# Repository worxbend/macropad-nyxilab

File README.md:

<div align="center">

# 🌙 nyxilab macropad

**12 keys. 2 screens. 16 LEDs. 1 stick *or* 1 knob. 0 glue.**
<br>it's giving main character desk energy 💅

**[✨ product page](https://worxbend.github.io/macropad-nyxilab/) · [📖 docs](https://worxbend.github.io/macropad-nyxilab/guide/) · [🧊 3D viewer](https://worxbend.github.io/macropad-nyxilab/guide/viewer.html) · [⬇️ downloads](https://worxbend.github.io/macropad-nyxilab/guide/downloads.html)**

</div>

## tl;dr 🫠

a hand-wired, 3D-printed macropad built around a **Raspberry Pi Pico 2**, with two color
displays, 16 RGB LEDs, and your pick of an analog thumbstick or a clicky rotary knob. this
monorepo has literally everything: the parametric case, print-ready files, blueprints,
a soldering guide with wiring maps, and the firmware. clone it, print it, solder it, flex it.
no custom PCB, no extra USB socket, no cap.

## choose your fighter 🎮

same case, same keys, same screens, same LEDs. only the thing in the middle changes,
and each edition is its own pair of projects.

| 🕹️ **joystick edition** | 🎛️ **rotary edition** |
|---|---|
|  |  |
| KY-023 thumbstick: mouse, scroll or arrow keys, per layer | KY-040 encoder + a chunky printed Ø48 knob: volume, undo/redo, scroll, zoom… |
| [`joystick/cad`](joystick/cad) · [`joystick/firmware`](joystick/firmware) | [`rotary/cad`](rotary/cad) · [`rotary/firmware`](rotary/firmware) |
| `nyxilab-macropad-joystick-pico2.uf2` | `nyxilab-macropad-rotary-pico2.uf2` |
| [read more →](joystick/README.md) | [read more →](rotary/README.md) |

the frame and the bar-display spine are literally the same parts in both, so switching
teams later means reprinting the top plate and the base. that's it.

## the specs (no cap) 📋

| | |
|---|---|
| ⌨️ **inputs** | 12 × MX switches (hand-wired matrix + diodes) and a KY-023 thumbstick that clicks **or** a KY-040 knob that clicks |
| 📺 **screens** | 1.9" 170×320 ST7789 IPS (main character) + 2.25" 76×284 ST7789P3 bar (the sidekick) |
| 💡 **lights** | 2 × 8 WS2812B LED sticks on the base, either side of the Pico: layer color, breathing or rainbow |
| 🧠 **brain** | Pico 2 (RP2350) USB-C clone, or the OG Pico (RP2040) if that's what you've got |
| 📐 **case** | 3-layer wedge: top plate, contrasting centre frame, base · 10° tilt · 159 × 98 mm · 18 → 35 mm tall |
| 🔩 **held together by** | 8 × M3×8 countersunk screws into heat-set inserts. zero glue, fully serviceable |
| ⚡ **firmware** | USB keyboard + media + mouse, layers, tap-hold, macros, joystick modes or per-layer knob bindings, LED effects |
| 🖥️ **host bridge** | optional: a tiny Linux daemon puts your PC's CPU, RAM, temps, network + your own text on a HOST layer, and its keys run commands |

## the lore 📜

every design decision had a reason, bestie. here's the tea:

- **three layers, two colors.** top plate + base in color A, the frame in color B, so you get
  that stripe all the way around. the screws pull the base and plate together *through* the frame,
  so the color seams close tight. no gaps, no drama.
- **print the frame translucent and the stripe glows.** the LED sticks sit on the base
  pointing up, so a clear or frosted PETG frame turns into a light band in your layer color.
  opaque frame? still works, just more subtle (the glow leaks around the stick).
- **all 8 screws are the same length.** the screw posts hang off the top plate, so the wedge
  doesn't make you buy three screw sizes. we love a consistent queen.
- **the Pico clone has no holes at the USB end** (rude). so the back wall thins down to 1.2 mm
  around the USB-C socket and holds it in place. any cable plugs in all the way. understood the assignment.
- **the joystick dome swings wider than you'd think** when you tilt it. posts hanging from the top
  plate would've been in the way, so the stick stands on tilted posts that grow out of the base.
- **the knob is panel-mounted like a real audio knob.** the encoder's M7 nut clamps the plate,
  a square pocket underneath stops it from spinning, and the printed knob's bore ends exactly at
  the shaft tip, so you just press it on until it stops. pressing it clicks the switch, not the knob
  down the shaft. a thin engraved ring sits under its brim, because a sunken well would've printed
  as a 34 mm bridge on the pretty side. no thanks.
- **the bar display only has holes at one end.** a tiny printed clamp (`bar_spine`) holds the
  other end. no glue, no hot-glue era.

<div align="center">

<br><sub>cross-sections through the stick / the knob, the main screen, the Pico and the USB-C port. every mm accounted for 🧮</sub>
</div>

## glamour shots 📸

| exploded (it's a whole stack) | the knob era |
|---|---|
|  |  |
| **the base: Pico + LED sticks** | **the back (USB-C, centered, obviously)** |
|  |  |
| **what's inside** | **the underside of the plate** |
|  |  |
| **flip it over: the Signature Edition engraving** | |
|  | |

wanna spin it around yourself? **[open the 3D viewer](https://worxbend.github.io/macropad-nyxilab/guide/viewer.html)**
(or `docs/viewer.html` offline): switch editions, orbit, explode the layers, slice it with a live
section plane, toggle parts. it's lowkey addictive.

## the screens are eating fr 📺

these are rendered by the **actual firmware code** running on your PC (`make ui-sim`), not a mockup.
the dots underneath are the 16 LEDs, as the firmware would light them. real ones know.

| MEDIA layer | EDIT layer, caps lock on | FN held |
|---|---|---|
|  |  |  |
| **knob: volume** | **knob: undo/redo** | **knob: zoom preset + rainbow** |
|  |  |  |

the 1.9" screen mirrors the physical key layout and lights up what you press. the middle
shows the stick, or a dial with 20 ticks that follows the knob and says what it does right
now. the bar shows your layers, the stick mode or knob function, NUM/CAPS/SCROLL straight
from your computer, and a keys-per-second graph so you can watch yourself go feral.

### the HOST layer: your PC, on your desk 🖥️

run `nyxd` on linux (one small rust binary) and the HOST layer becomes a live dashboard:
CPU per core, temps, RAM, swap, disk, network, GPU, the clock, plus up to four lines of
whatever you pipe in with `nyxctl text 0 "build passed"`. two more pages: SWAY (your sway
workspaces + the focused window, keys 1-8 jump there) and PLAY (whatever MPRIS player is
playing, with play/pause, skip, seek and volume keys, via `playerctl`). the H1-H8 keys fire
shell commands on your PC. no daemon? the layer just hides itself. setup + protocol:
[docs/host-bridge.md](docs/host-bridge.md).

## soldering, but make it not scary 🔥

no PCB means you wire it yourself. the [soldering guide](docs/soldering.md) walks you through
it with pictures: how the matrix works, which way the diodes go, how the bent diode legs
*become* the row wires, and a wiring map drawn from the CAD model that shows where every
wire runs inside the case (plate seen from below, base from above).

| the diode, step by step | where the wires run |
|---|---|
|  |  |

## what's in the box 📦

four projects and the stuff they share:

```
joystick/
  cad/               the joystick edition's case: edition.py + build.py, exports/ (STL, 3MF, STEP, FreeCAD, GLB, blueprints)
  firmware/          its PlatformIO project: config.h, keymap.cpp, the stick, tests, dist/*.uf2
rotary/
  cad/               the rotary edition's case: the encoder mount + the knob, exports/
  firmware/          its PlatformIO project: config.h, keymap.cpp, the knob, tests, dist/*.uf2
common/
  cad/               the shared parametric case model (build123d) that both editions build on
  firmware/          the shared firmware libraries: engine, USB HID, displays, LEDs, the app loop (+ their tests)
docs/                design notes, printing, soldering, wiring, assembly, generated images, 3D viewer
tools/               UI simulator, wiring diagrams + maps, soldering figures, viewer + website builders
```

## speedrun any% 🏃‍♀️

1. **pick your edition** (joystick or rotary) and grab its files: `<edition>/cad/exports/` or the
   [downloads page](https://worxbend.github.io/macropad-nyxilab/guide/downloads.html).
2. **print the fit tests first** (`3mf/fit-tests/`, ~1 h total). they check the switch
   cut-out, both display pockets, the USB-C port, the joystick posts or the encoder mount,
   and the LED-stick posts against *your* parts. rotary gang: print the knob early too.
   something off? measure it, tweak `common/cad/macropad_cad/params.py` (or the edition's
   `edition.py`), run `make cad`. easy.
3. **print the case**: `top_plate` (color A, top face down), `frame` (color B, translucent if you
   want the glow), `base` (color A), the tiny `bar_spine`, the `ballast` (flat bottom down,
   100 % infill), and the `knob` for the rotary edition.
   settings in [docs/printing.md](docs/printing.md).
4. **solder it and put it together**: the [build guide](docs/build-guide.md) is the route, with
   [docs/soldering.md](docs/soldering.md) → [docs/wiring.md](docs/wiring.md) →
   [docs/assembly.md](docs/assembly.md) for the details.
   the LED sticks need one diode and one resistor, no board.
5. **flash it**: hold BOOTSEL while plugging in the Pico, drop
   `joystick/firmware/dist/nyxilab-macropad-joystick-pico2.uf2` (or the rotary one) onto the
   `RP2350` drive (or `make flash-joystick` / `make flash-rotary`). after that, flashing reboots
   it for you, no button needed. W.

> [!WARNING]
> **red flags 🚩 read before printing.** a few dimensions came from photos, not datasheets:
> how far the Pico's USB-C sticks out past the board, the bar display's glass and hole positions,
> the joystick's hole spacing, the KY-040's shaft length, and the LED sticks' hole spacing.
> they're tagged `MEASURE` in the params. grab your calipers, or at least print the fit tests.
> skipping this is a skill issue.

> [!TIP]
> image upside down on a screen? pointer going the wrong way? knob turning backwards?
> that's one setting each in `<edition>/firmware/include/config.h` (`*_ROTATION`, `JOY_INVERT_X/Y`,
> `ENC_REVERSE`, or just FN + REV on the pad). the [firmware README](common/firmware/README.md) has the full list.

## build from source (for the terminally online) 🛠️

```bash
make setup              # Python venv for the CAD + docs tools, PlatformIO
make cad                # both editions: fit checks, exports, renders, blueprints (~5 min)
make firmware           # both editions for the Pico 2, UF2s land in <edition>/firmware/dist/
make test               # all unit tests on your PC (shared core, stick maths, knob decoder)
make docs               # UI renders, wiring diagrams + maps, soldering figures, 3D viewer, the website
```

one edition at a time: `make cad-rotary`, `make firmware-joystick`, `make test-rotary`, and so on.
the FreeCAD files rebuild when `freecadcmd` is on your PATH (or set `FREECAD_CMD=/path/to/freecadcmd`).
everything else only needs Python and PlatformIO (and Rust for the optional host bridge). the website in `site/` is what
[GitHub Pages](https://worxbend.github.io/macropad-nyxilab/) serves; it redeploys on every push to `main`.

```mermaid
flowchart LR
  subgraph core0["core 0 · the grind"]
    scan["matrix scan 1 kHz"] --> deb["debounce 5 ms"] --> eng["engine: layers, tap-hold, macros, knob"] --> usb["USB HID"]
    centre["stick ADC or knob interrupts"] --> eng
  end
  subgraph core1["core 1 · the aesthetic"]
    main["1.9in screen"]
    bar["2.25in bar"]
    leds["16 RGB LEDs"]
  end
  eng -. "UI snapshot" .-> main
  eng -. "UI snapshot" .-> bar
  eng -. "UI snapshot" .-> leds
```

## receipts 🧾

we don't just vibe, we verify:

- **192 collision checks** (joystick) and **215** (rotary) on every build: each printed part
  against each component (plus room for solder joints and wiring), against the joystick's full
  25° swing or the spinning knob, and every component against every other, LED sticks
  included. **0 clashes.**
- **printability check** in print orientation: no supports needed, only a few short bridges (the longest is a 10.5 mm foot recess).
- **37 firmware unit tests** (debounce, layers, tap-hold, macros, knob bindings, LED effects and
  the current limit in the shared core; the stick maths; the knob decoder), all green ✅
- USB delivery, settings and centre-control regressions for both editions run with
  mocked hardware via `make test-hardware`.
- both editions build for **both** boards (Pico 2 / OG Pico) with **zero warnings** under `-Wall -Wextra`.
- the wiring diagrams are generated from each edition's `config.h`, and the build refuses if the two
  editions ever disagree on a shared pin.

## faq 💬

**joystick or knob?** stick if you want a mouse, arrows and scrolling with your thumb. knob if
you live in volume, timelines and undo history. both are in this repo and share almost every part.

**do I need the LEDs?** nope. leave them out, the posts don't care. set `LED_COUNT = 0` if you
want the firmware to stop talking to GP28.

**will 16 LEDs cook my USB port?** no. the firmware caps them at 250 mA total, and they dim with
the screens and switch off when your computer sleeps.

**does it need supports?** nah. every part prints flat as exported.

**glue?** zero. it's screws all the way down, so you can open it up and fix your wiring later.

**can I use the OG Pico (RP2040)?** yes bestie, `make firmware-joystick-pico` (or `-rotary-pico`)
and flash the `…-pico.uf2`. same footprint, same case.

**what do the keys do?** four layers out of the box: MEDIA, EDIT, F1–F24 (three pages of eight) and a hold-for-FN layer.
tap the front-left key for the next layer, hold it for FN. the knob does volume, undo/redo,
scroll and screen brightness depending on the layer, and FN + KNOB swaps in volume / scroll /
zoom / arrows. remap everything in `<edition>/firmware/src/keymap.cpp`.

**macOS?** the shortcuts use Ctrl. swap `MOD_LCTRL` for `MOD_LGUI` in the keymap and you're golden.

## docs (the boring-but-important era) 📚

everything below is also on the **[guide site](https://worxbend.github.io/macropad-nyxilab/guide/)**, rendered nicely.

- **[3D viewer](https://worxbend.github.io/macropad-nyxilab/guide/viewer.html)**: both editions. orbit, explode, section, toggle parts
- [design notes](docs/design.md): layout, the 3-layer stack, how each part is held, what the checks verify
- [printing](docs/printing.md): orientation, settings, colors, the knob, the dimensions to verify first
- [build guide](docs/build-guide.md): solder, wire, flash, assemble, in order, with a test after every stage
- [PCB build](docs/pcb-build.md): the same pad with three boards and two flat cables instead of hand wiring: what PCBWay makes turnkey, what to buy, print and assemble
- [soldering](docs/soldering.md): tools, the matrix, diodes step by step, displays, LEDs, the Pico, wiring maps, troubleshooting
- [wiring](docs/wiring.md): Pico pin map, matrix, displays, joystick, encoder, LED sticks
- [assembly](docs/assembly.md): bill of materials + step-by-step build, both editions
- [joystick edition](joystick/README.md) · [rotary edition](rotary/README.md): what is specific to each
- [firmware](common/firmware/README.md): keymap, layers, joystick modes, knob bindings, LED modes, display settings, serial console
- [CAD](common/cad/README.md): the shared model, the edition hooks, changing parameters and regenerating the files

<div align="center">
<br>
made with 💜, calipers, and way too many clearance checks
<br>
<sub>touch grass after soldering. you earned it 🌱</sub>
</div>

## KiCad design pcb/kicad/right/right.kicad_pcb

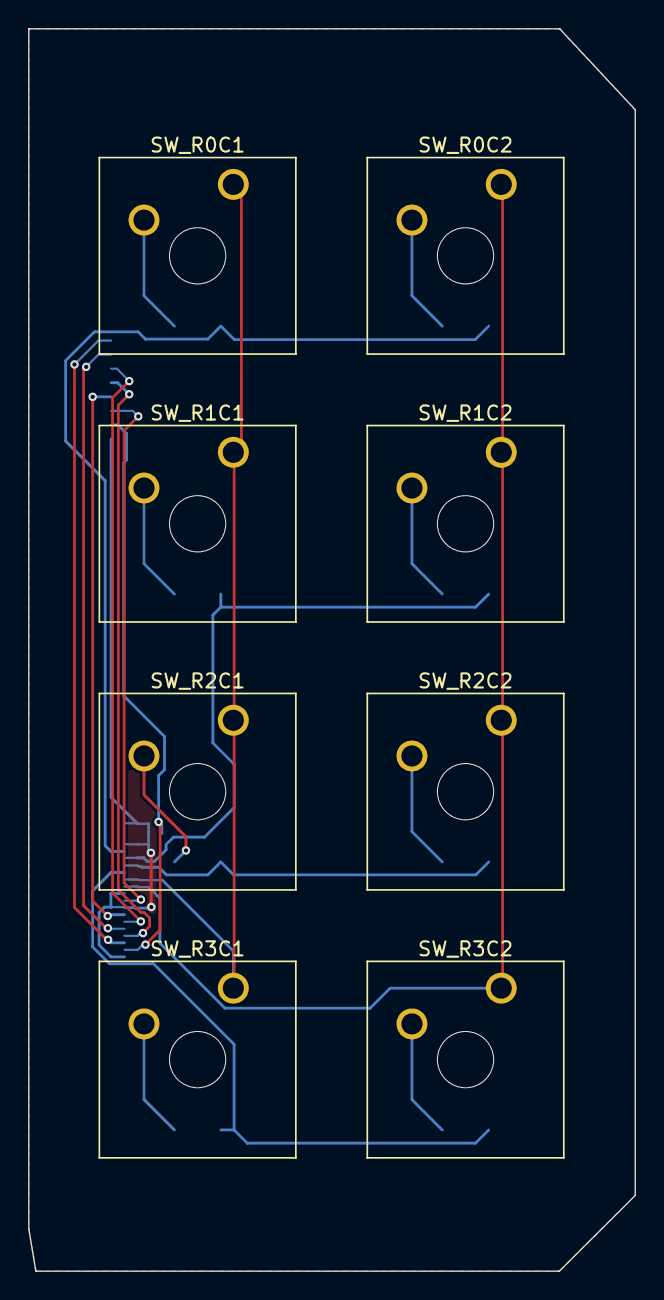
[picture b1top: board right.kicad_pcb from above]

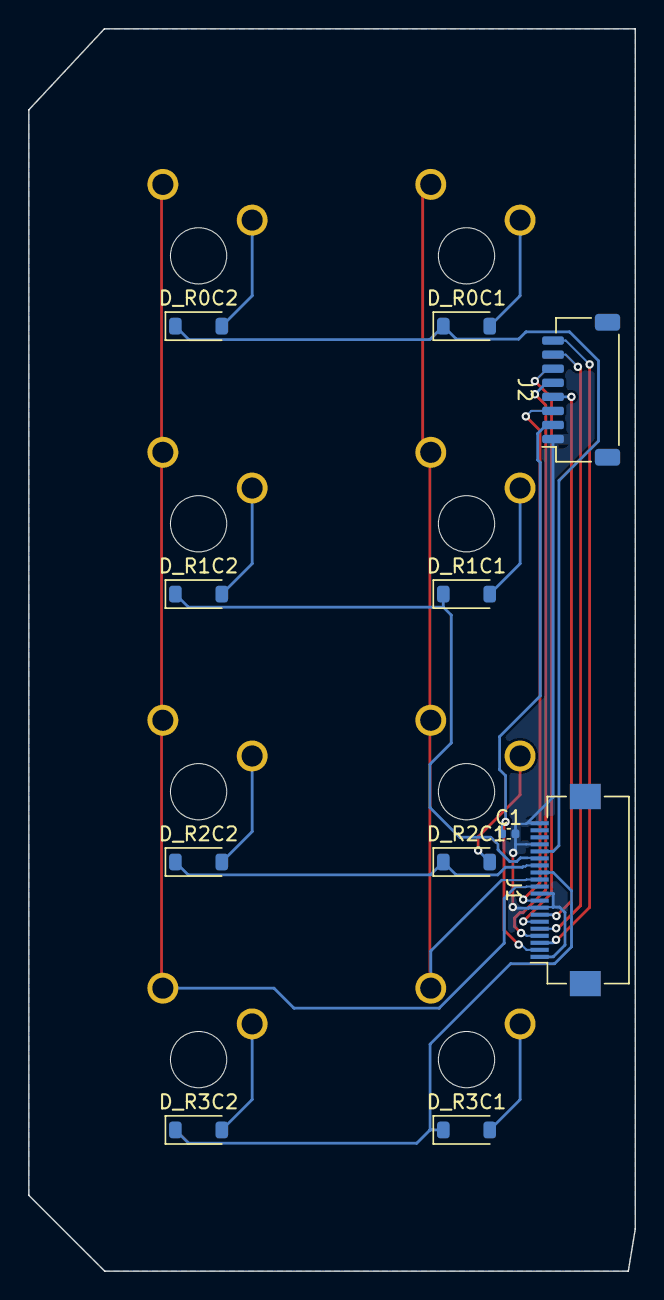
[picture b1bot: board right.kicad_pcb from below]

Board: 2 copper layers, 43.1 x 88.3 mm, 19 parts (11 on the bottom side), 22 nets.

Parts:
C1: 100nF; C_0402_1005Metric
D_R0C1, D_R0C2, D_R1C1, D_R1C2, D_R2C1, D_R2C2, D_R3C1, D_R3C2: 1N4148W; D_SOD-123
J1: FPC 20-pin 0.5 mm; Hirose_FH12-20S-0.5SH_1x20-1MP_P0.50mm_Horizontal
J2: JST-SH 8; JST_SH_SM08B-SRSS-TB_1x08-1MP_P1.00mm_Horizontal
SW_R0C1, SW_R0C2, SW_R1C1, SW_R1C2, SW_R2C1, SW_R2C2, SW_R3C1, SW_R3C2: MX switch; SW_Cherry_MX_1.00u_Plate

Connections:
3V3: C1.1, J1.2, J2.2
COL1: J1.12, SW_R0C1.1, SW_R1C1.1, SW_R2C1.1, SW_R3C1.1
COL2: J1.11, SW_R0C2.1, SW_R1C2.1, SW_R2C2.1, SW_R3C2.1
GND: C1.2, J1.1, J1.8, J1.10, J1.17, J1.20, J2.1
MAIN_BL: J1.3, J2.8
MAIN_CS: J1.5, J2.7
MAIN_DC: J1.6, J2.6
MAIN_MOSI: J1.7, J2.4
MAIN_RST: J1.4, J2.5
MAIN_SCK: J1.9, J2.3
N_R0C1: D_R0C1.2, SW_R0C1.2
N_R0C2: D_R0C2.2, SW_R0C2.2
N_R1C1: D_R1C1.2, SW_R1C1.2
N_R1C2: D_R1C2.2, SW_R1C2.2
N_R2C1: D_R2C1.2, SW_R2C1.2
N_R2C2: D_R2C2.2, SW_R2C2.2
N_R3C1: D_R3C1.2, SW_R3C1.2
N_R3C2: D_R3C2.2, SW_R3C2.2
ROW0: D_R0C1.1, D_R0C2.1, J1.16
ROW1: D_R1C1.1, D_R1C2.1, J1.15
ROW2: D_R2C1.1, D_R2C2.1, J1.14
ROW3: D_R3C1.1, D_R3C2.1, J1.13

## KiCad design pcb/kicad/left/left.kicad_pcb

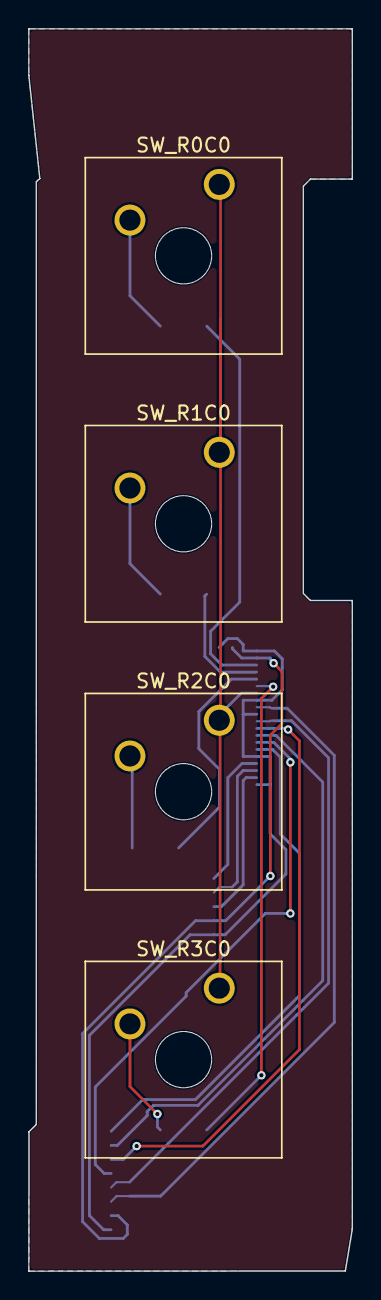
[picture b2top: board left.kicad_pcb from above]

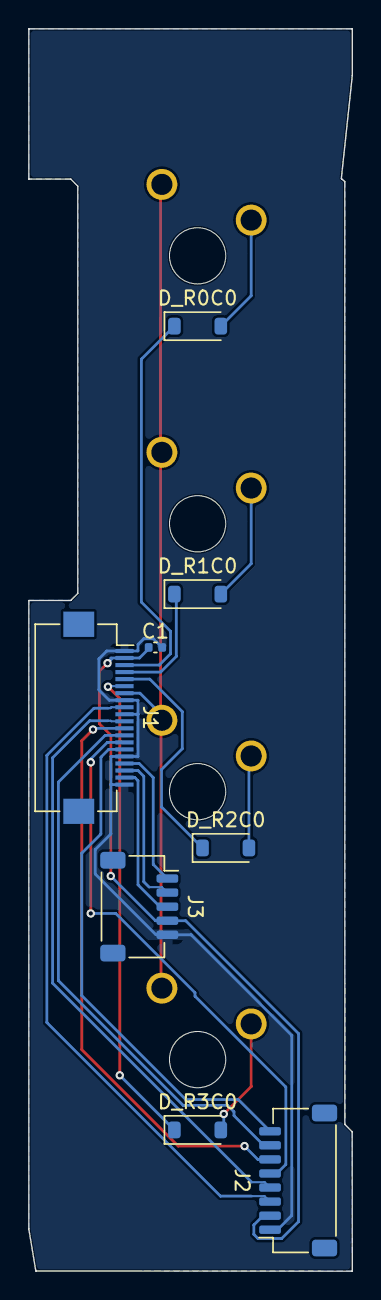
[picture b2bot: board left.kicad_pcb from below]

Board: 2 copper layers, 23.0 x 88.3 mm, 12 parts (8 on the bottom side), 20 nets.

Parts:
C1: 100nF; C_0402_1005Metric
D_R0C0, D_R1C0, D_R2C0, D_R3C0: 1N4148W; D_SOD-123
J1: FPC 20-pin 0.5 mm; Hirose_FH12-20S-0.5SH_1x20-1MP_P0.50mm_Horizontal
J2: JST-SH 8; JST_SH_SM08B-SRSS-TB_1x08-1MP_P1.00mm_Horizontal
J3: JST-SH 5; JST_SH_SM05B-SRSS-TB_1x05-1MP_P1.00mm_Horizontal
SW_R0C0, SW_R1C0, SW_R2C0, SW_R3C0: MX switch; SW_Cherry_MX_1.00u_Plate

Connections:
3V3: C1.1, J1.2, J2.2, J3.4
BAR_BL: J1.15, J2.8
BAR_CS: J1.13, J2.7
BAR_DC: J1.12, J2.6
BAR_MOSI: J1.11, J2.4
BAR_RST: J1.14, J2.5
BAR_SCK: J1.9, J2.3
COL0: J1.7, SW_R0C0.1, SW_R1C0.1, SW_R2C0.1, SW_R3C0.1
C_A: J1.17, J3.1
C_B: J1.18, J3.2
C_SW: J1.19, J3.3
GND: C1.2, J1.1, J1.8, J1.10, J1.16, J1.20, J2.1, J3.5
N_R0C0: D_R0C0.2, SW_R0C0.2
N_R1C0: D_R1C0.2, SW_R1C0.2
N_R2C0: D_R2C0.2, SW_R2C0.2
N_R3C0: D_R3C0.2, SW_R3C0.2
ROW0: D_R0C0.1, J1.3
ROW1: D_R1C0.1, J1.4
ROW2: D_R2C0.1, J1.5
ROW3: D_R3C0.1, J1.6

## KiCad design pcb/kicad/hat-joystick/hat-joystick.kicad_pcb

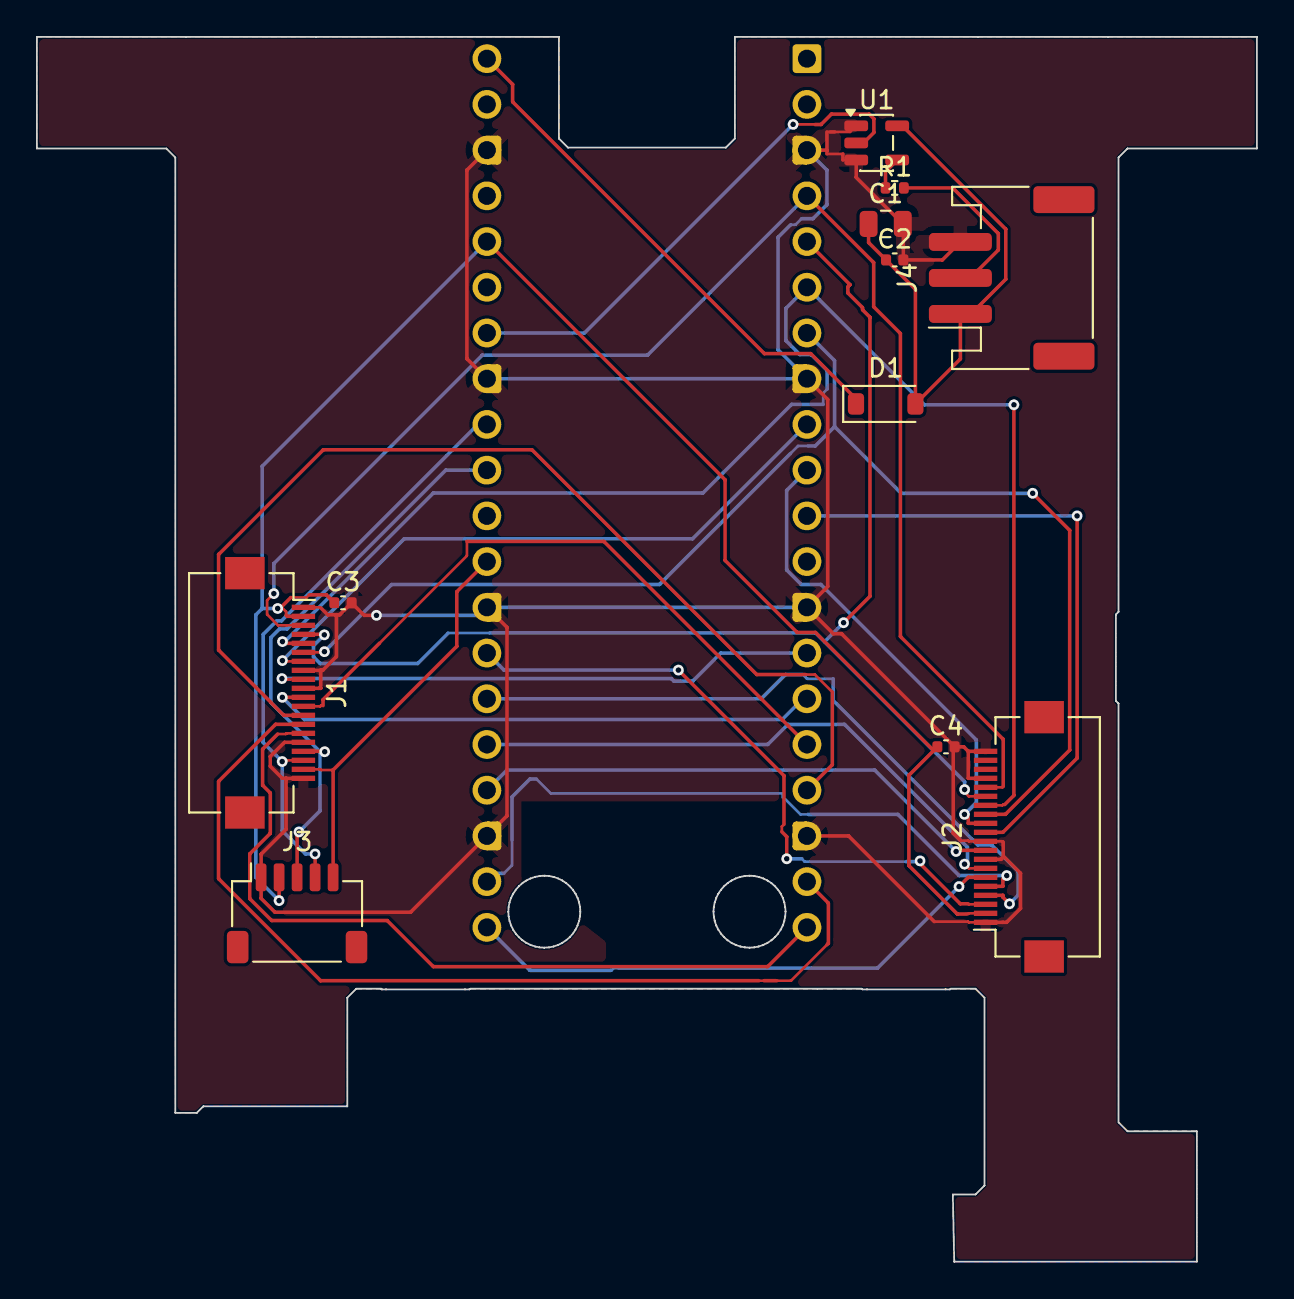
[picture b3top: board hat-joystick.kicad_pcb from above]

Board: 2 copper layers, 67.8 x 68.0 mm, 12 parts (1 on the bottom side), 29 nets.

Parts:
C1: 10uF; C_0805_2012Metric
C2, C3, C4: 100nF; C_0402_1005Metric
D1: B5819W; D_SOD-123
H1: Raspberry Pi Pico 2 (below the hat); RaspberryPi_Pico_Common_THT
J1, J2: FPC 20-pin 0.5 mm; Hirose_FH12-20S-0.5SH_1x20-1MP_P0.50mm_Horizontal
J3: JST-SH 5; JST_SH_SM05B-SRSS-TB_1x05-1MP_P1.00mm_Horizontal
J4: JST-PH 3; JST_PH_S3B-PH-SM4-TB_1x03-1MP_P2.00mm_Horizontal
R1: 330R; R_0402_1005Metric
U1: 74AHCT1G125; SOT-23-5

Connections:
3V3: C3.1, C4.1, H1.36, J1.2, J2.2, J3.2
BAR_BL: H1.20, J1.15
BAR_CS: H1.17, J1.13
BAR_DC: H1.16, J1.12
BAR_MOSI: H1.15, J1.11
BAR_RST: H1.19, J1.14
BAR_SCK: H1.14, J1.9
COL0: H1.9, J1.7
COL1: H1.10, J2.12
COL2: H1.11, J2.11
C_A: H1.31, J1.17, J3.3
C_B: H1.32, J1.18, J3.4
C_SW: H1.29, J1.19, J3.5
GND: C1.2, C2.2, C3.2, C4.2, H1.3, H1.8, H1.13, H1.18, H1.23, H1.28, H1.33, H1.38, J1.1, J1.8, J1.10, J1.16, J1.20, J2.1, J2.8, J2.10, J2.17, J2.20, J3.1, J4.3, U1.1, U1.3
LED_5V: C1.1, C2.1, D1.2, J4.1, U1.5
LED_DATA: H1.34, U1.2
LED_DIN: J4.2, R1.2
LED_Y: R1.1, U1.4
MAIN_BL: H1.27, J2.3
MAIN_CS: H1.22, J2.5
MAIN_DC: H1.21, J2.6
MAIN_MOSI: H1.25, J2.7
MAIN_RST: H1.26, J2.4
MAIN_SCK: H1.24, J2.9
ROW0: H1.4, J1.3, J2.16
ROW1: H1.5, J1.4, J2.15
ROW2: H1.6, J1.5, J2.14
ROW3: H1.7, J1.6, J2.13
VBUS: D1.1, H1.40

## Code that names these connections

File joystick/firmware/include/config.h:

// ============================================================================
//  Hardware configuration, JOYSTICK edition - pins match docs/wiring.md
//
//  Raspberry Pi Pico 2 (RP2350) or Pico (RP2040), USB-C clone boards.
//  "GPx" numbers below are GPIO numbers, not physical pin numbers.
// ============================================================================
#pragma once
#include <stdint.h>

#include "core/keymap.h"

namespace cfg {

constexpr uint8_t SETTINGS_EDITION = 1;  // persistent centre data belongs to the joystick

// ---- key matrix, COL2ROW: diode cathode (black band) towards the ROW wire --
constexpr uint8_t ROW_PINS[mp::ROWS] = {2, 3, 4, 5};  // R0 = back row ... R3 = front row
constexpr uint8_t COL_PINS[mp::COLS] = {6, 7, 8};     // C0 = left column, C1/C2 = right block
constexpr uint8_t DEBOUNCE_MS = 5;
constexpr uint32_t SCAN_INTERVAL_US = 1000;

// ---- KY-023 joystick.  Power it from 3V3 (pin 36), NOT 5 V: the ADC is 3.3 V max
constexpr uint8_t JOY_X_PIN = 26;   // ADC0  (module pin VRx)
constexpr uint8_t JOY_Y_PIN = 27;   // ADC1  (module pin VRy)
constexpr uint8_t JOY_SW_PIN = 22;  // module pin SW, internal pull-up
constexpr bool JOY_INVERT_X = false;  // flip if the pointer moves the wrong way
constexpr bool JOY_INVERT_Y = false;
constexpr bool JOY_SWAP_XY = false;
constexpr uint32_t JOY_PERIOD_MS = 8;

// ---- RGB LED sticks on the base: 2 x 8 WS2812B (CJMCU-2812-8), chained --------------
//  right stick DIN (back end) <- GP28 via 330 R; its DOUT (front) -> left stick DIN.
//  5V from VBUS (pin 40) through a 1N4001 diode, so 3.3 V data is a valid "high".
constexpr uint8_t LED_PIN = 28;
constexpr uint8_t LED_COUNT = 16;            // 0 = no LED sticks fitted
constexpr uint8_t LED_MAX_BRIGHTNESS = 89;   // 35 % of 255: the cap at LED level 8, on top of DIM-/DIM+
constexpr uint16_t LED_BUDGET_MA = 250;      // hard limit for the sticks; USB 2.0 gives 500 mA in total

// ---- main display: 1.9" 170x320 ST7789 on SPI0 ---------------------------------
constexpr uint8_t MAIN_SCK = 18, MAIN_MOSI = 19, MAIN_CS = 17, MAIN_DC = 16, MAIN_RST = 20, MAIN_BL = 21;
constexpr uint16_t MAIN_W = 170, MAIN_H = 320;  // native panel size
constexpr uint8_t MAIN_ROTATION = 1;            // landscape; use 3 if the image is upside down
constexpr bool MAIN_INVERT = true;              // IPS panels need colour inversion
constexpr bool MAIN_BGR = false;                // set if red and blue are swapped

// ---- bar display: 2.25" 76x284 ST7789P3 on SPI1 --------------------------------
constexpr uint8_t BAR_SCK = 10, BAR_MOSI = 11, BAR_CS = 13, BAR_DC = 12, BAR_RST = 14, BAR_BL = 15;
constexpr uint16_t BAR_W = 76, BAR_H = 284;
constexpr uint8_t BAR_ROTATION = 0;  // portrait, the way the case holds the module (seen on a build); use 2 if upside down
constexpr bool BAR_INVERT = true;
constexpr bool BAR_BGR = false;

// The SPI clock is the system clock divided by an even number, rounded down to this value:
// Pico 2 (150 MHz): 40 and 62.5 MHz both give 37.5 MHz, 75 MHz gives 75.  Pico (125 MHz, set in platformio.ini):
// 40 MHz gives 31.25, 62.5 gives 62.5.
constexpr uint32_t SPI_HZ = 40000000;  // safe for hand-wired leads; 20 MHz if glitchy

// ---- backlight & idle ------------------------------------------------------------
constexpr uint8_t BRIGHTNESS_DEFAULT = 200;  // 0..255
constexpr uint8_t BRIGHTNESS_STEP = 32;
constexpr uint32_t DIM_AFTER_MS = 60UL * 1000;       // dim after 1 min idle
constexpr uint32_t SLEEP_AFTER_MS = 10UL * 60 * 1000;  // backlight off after 10 min
constexpr uint8_t BRIGHTNESS_DIMMED = 24;

// ---- USB --------------------------------------------------------------------------
constexpr const char* USB_VENDOR_NAME = "Nyxilab";
constexpr const char* USB_PRODUCT_NAME = "Nyxilab Macropad";
// Host bridge: a second (vendor) HID interface for the daemon in host/, which feeds
// the HOST layer's dashboard.  false = no extra interface, HOST layers stay hidden.
constexpr bool HOST_LINK = true;

}  // namespace cfg

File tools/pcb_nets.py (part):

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    **{f"COL{i}": ("COL_PINS", i) for i in range(3)},
    **{f"MAIN_{s}": (f"MAIN_{s}", None) for s in ("SCK", "MOSI", "CS", "DC", "RST", "BL")},
    **{f"BAR_{s}": (f"BAR_{s}", None) for s in ("SCK", "MOSI", "CS", "DC", "RST", "BL")},
    "LED_DATA": ("LED_PIN", None),
}
CENTRE = {  # net -> config.h name per edition
    "C_A": {"rotary": "ENC_A_PIN", "joystick": "JOY_X_PIN"},
    "C_B": {"rotary": "ENC_B_PIN", "joystick": "JOY_Y_PIN"},
    "C_SW": {"rotary": "ENC_SW_PIN", "joystick": "JOY_SW_PIN"},
}

# Flat cables (20-pin, 0.5 mm FFC), pin 1 .. 20.  GND next to each SPI clock and data line and at both edges; 3V3 on
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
